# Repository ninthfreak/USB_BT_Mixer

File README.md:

# USB_BT_Mixer

A small box with two USB-C inputs and one Bluetooth audio output. Any USB-C host that supports USB audio sees each input as a normal USB sound card. The box mixes both inputs and streams the mix to any Bluetooth audio sink.

- **Architecture (start here): [`docs/architecture.md`](docs/architecture.md)**
- Decision log: [`docs/decisions.md`](docs/decisions.md)
- Design record: [`docs/HANDOFF.md`](docs/HANDOFF.md)
- Corrections since the handoff: [`docs/review-notes.md`](docs/review-notes.md)
- Design envelope (limits and extension points): [`docs/design-envelope.md`](docs/design-envelope.md)
- Viability review: [`docs/viability-review.md`](docs/viability-review.md)
- Parts list: [`hardware/BOM.csv`](hardware/BOM.csv)

Status: planning. Inputs: Waveshare RP2350-USB-C ×2, USB-C exposed directly through the enclosure (each needs an external Schottky to the shared rail). Bluetooth output: original ESP32 on a Waveshare ESP32-DEV-KIT-WROOM-32E-N4, powered from the rail via its `VSYS` pin. The ESP32 mixes and owns the audio clock. Configured from any browser via a page the box serves over USB; no case buttons. See [`docs/decisions.md`](docs/decisions.md). Firmware not started; the enclosure test coupon needs re-measuring for the new input board.

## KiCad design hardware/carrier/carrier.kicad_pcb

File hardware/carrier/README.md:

# Carrier board

> **Status: KiCad DRC clean, routed, not built, not ordered.**
>
> - **Antenna clearance: accepted as is** (owner, 2026-10-26). Copper is
>   6.55 mm in front of the antenna against Espressif's 15 mm; the antenna
>   itself hangs fully past the board edge
>   ([`AUDIT.md` #21](AUDIT.md#21-antenna-clearance-on-the-front-side-new)).
> - Recommendation before ordering: **the two-I2S clock loop-back is still
>   untested.** A jumper-wire bench test of one input board + the ESP32 would
>   prove it for the price of an afternoon.

One flat PCB that the three modules solder onto, replacing the hand-wired
loom. All passives are through-hole and live on it.

## At a glance

| | |
|---|---|
| Size | 70.0 × 79.6 mm, L-shaped (see below), 2 layers, 1.6 mm |
| Parts | U1, U2 input boards; U3 ESP32 devkit; 2 Schottky diodes; 9 resistors (R1, R3 standing); 4 capacitors; 3-pin debug header; 2 test pads |
| Nets | 22: 18 signal, 3 power (VBUS1, VBUS2, RAIL), GND |
| Rules | 0.40 mm track, 0.25 mm clearance, 0.8/0.4 mm vias, 0.5 mm copper to edge, 0.5 mm drill to drill. Loose for any fab |
| Top layer | **Every signal.** No signal changes layer: 0 signal vias |
| Bottom layer | Ground plane (89 % of the board) plus power only |
| Routing | Freerouting: 108 signal segments; rail and ground stubs by hand; 754 mm of track; 4 vias, all ground |
| Joints to solder | 40 of 70 module lands, plus the passives |

## How the board is laid out

The rules, so it reads the way it works (owner, 2026-10-27):

- **Top layer: signals.** Every signal stays on top from end to end.
- **Bottom layer: ground and power.** A solid ground plane. The rail is the
  only long track on it, running round the front and left edges behind the
  input boards' port ends, where no signal crosses it.
- **Related lines run together.** Each board's three I2S lines and its UART
  pair travel as groups.

Each input board is **turned so its native USB port faces the hosts** (the
"programming" port, whose shell hangs 1 mm past the front edge). Its PIO-USB
port faces inward, unused. See review-notes #25.

Seen from the ESP32, west to east, the board carries input 1's UART pair,
input 1's I2S group, input 2's UART pair, input 2's I2S group. The ESP32 pins
are chosen in that order (`netlist.py`). The shared clocks reach input 2 by
passing **between the pads of R2 and R4**, which lie across input 2's UART
pair, so no signal needs the bottom layer.

| Where | What |
|---|---|
| Left margin | The rail (bottom), test points |
| Strip behind input 1 | Rail bulk and bypass at the ESP32's 5V pad; input 1's clock resistors R1, R3, standing on their lanes |
| Channel between the boards | Input 1's diode, bypass and GP29 pull-down at its power pads; debug header J1; input 2's RX resistor R6 on its lane |
| Strip behind input 2 | Input 2's clock resistors R2, R4, lying across its UART pair; its GP29 and audio pull-downs |
| Right margin | Input 2's diode and bypass at its power pads |
| Behind the ESP32 | Input 1's RX resistor R5, at the ESP32's TX pin |

## Why it is an L, not a rectangle

The front must be 70 mm wide for the two input boards side by side. The ESP32
devkit sits across the back, its USB-C end hanging 1 mm past the left edge so
a flashing cable fits. That puts the antenna at the right.

Espressif's first choice is an antenna **outside** the base board, with any
board under it cut away. So the back-right corner is cut off and the
devkit's antenna end hangs 7.5 mm into free air. An L costs nothing extra:
fabs price by the bounding box.

The catch is the antenna's front side, where the front-right block comes
close: 6.55 mm, where Espressif asks for 15. The owner accepted that rather
than make the board ~8.5 mm deeper ([AUDIT.md #21](AUDIT.md#21-antenna-clearance-on-the-front-side-new)).

## Build

```sh
./build.sh                          # regenerate and check everything
/usr/bin/python3 route.py --reroute # only after moving parts or changing nets
```

Everything runs under the **system** python (`/usr/bin/python3`), which has
KiCad 7's `pcbnew` bindings. Every step must pass. The output is
byte-identical across rebuilds, so a diff means something really changed.

The build does **not** run Freerouting: its output varies from run to run.
It lays the committed result, `carrier.ses`. If the placement or netlist has
changed since that route was made, `route.py` stops and says to reroute.
Rerouting downloads Freerouting 2.1.0 once (SHA-256 checked, analytics off)
and needs Java 17 or later; it takes about 10 seconds.

`carrier.kicad_sch`, `carrier.kicad_pcb`, `carrier.pretty/`,
`CONNECTIONS.md` and the PDFs are generated. Edit `netlist.py` (connectivity)
or `gen_pcb.py` (placement) and rebuild. Never hand-edit the outputs.

## Files

| File | What |
|---|---|
| `netlist.py` | **Single source of truth** for connectivity: parts, pin maps, nets, footprints, and what is deliberately unconnected |
| `gen_fp.py` | The two module land patterns, from `enclosure/boards.scad` |
| `gen_sch.py` | `carrier.kicad_sch` |
| `gen_table.py` | `CONNECTIONS.md`: every net, and which pads to solder |
| `gen_pcb.py` | `carrier.kicad_pcb`, built with pcbnew: outline, placement, pad nets, schematic links, labels, the ground pour |
| `route.py` | Lays the rail and ground stubs by hand, every signal from `carrier.ses`; `--reroute` runs Freerouting to make a new one |
| `specctra.py` | Design export edits and session import between KiCad and Freerouting |
| `carrier.ses`, `carrier-route.json` | The committed route, and the hash of the design it was made for |
| `drc.py` | **The gate.** KiCad's own DRC with this board's rules, plus every pad's net against `netlist.py` |
| `check_footprints.py` | Recomputes every pad coordinate from `boards.scad` |
| `check_netlist.py` | Reads the netlist back out of the schematic and diffs it; checks diode and capacitor polarity against the footprint's own markings |
| `check_pcb.py` | Mechanical intent: native USB ports over the front edge, ESP32 overhangs at both ends, hole webs |
| `check_routing.py` | Routed intent: power widths, I2S chain lengths, bottom pour coverage, every signal on top |
| `AUDIT.md` | The 2026-10-26 audit and what was done about each finding |

## How it is verified

KiCad's DRC (`pcbnew.WriteDRCReport`) is the authority: clearances,
connectivity including the pour, courtyards, holes, silkscreen, keep-outs.
KiCad 7's `kicad-cli` has no DRC command, which for a while was taken to mean
no DRC was available. It was, through the Python bindings.

The custom checks cover what DRC cannot know: design intent. Each one has
been shown to **fail** on a deliberately broken board, not only to pass:

| Break | Caught by | Result |
|---|---|---|
| Diode pins mapped A=1 (the original bug) | `check_netlist.py` | 4 polarity failures |
| Delete the longest BCLK1 track | `drc.py` | 1 unconnected, 2 dangling |
| Empty the GND pour | `drc.py` | many unconnected |
| Drop a GND via onto an LRCK track | `drc.py` | clearance and hole errors |
| Track 0.3 mm from the edge | `drc.py` | edge clearance |
| Power traces at 0.4 mm | `check_routing.py` | every thin RAIL segment listed |
| A BCLK track on the bottom, a via on BCLK1 | `check_routing.py` | both listed |
| ESP32 USB-C end flush (no overhang) | `check_pcb.py` | fails |
| Antenna overhang 3 mm | `check_pcb.py` | fails |
| Input 1 turned back to 0° (PIO-USB to the hosts) | `check_pcb.py` | fails |
| R8 moved 1 mm, old route laid | `route.py` | refuses: "routed for a different placement" |

One KiCad behaviour worth knowing when testing: saving a board reassigns a
track that is not connected to its own net to whatever copper it touches (in
practice, the ground pour). A test track must therefore join two pads of its
net. DRC still catches the missing connection a reassigned track leaves.

`drc-report.txt` holds the last report. Its only entries are
"library not in this configuration" notes: the container has no global KiCad
library table. They say nothing about the copper.

## Pin numbering

We draw both the symbol and the footprint, so the numbering is ours.

**RP2350-USB-C** — component side, native ("programming") port at the top:

- pads 1–9, left edge top to bottom: `5V GND 3V3 GP29 GP28 GP27 GP26 GP10 GP9`
- pads 10–18, right edge top to bottom: `GP0 GP1 GP2 GP3 GP4 GP5 GP6 GP7 GP8`

On the carrier each input board is turned 180°, so the native port faces the
front edge, power and I2S are on the board's right-hand edge and UART/debug
on its left.

**ESP32-DEV-KIT** — pads 1–19 are header J3, pads 20–38 are J4 (so J4 pin *n*
is our pad 19 + *n*). Pads 1, 2, 20 and 21 have no land: they sit under the
antenna overhang.

## Land patterns

Both modules are castellated, so they solder flat with the iron on the
**outside** of every joint: visible, inspectable, reworkable, no reflow.

Each pad is 1.30 mm along the edge × 3.00 mm across, sticking out 1.10 mm past
the module outline. At 2.54 mm pitch that leaves 1.24 mm between pads. The
pads reference the board **outline**, so the ESP32's header row spacing never
enters the footprint.

| Footprint | +Y is |
|---|---|
| `RP2350-USB-C` | the **native USB** ("programming") port, proud of the edge. Placed at 180°, so +Y faces the front edge |
| `ESP32-DEV-KIT` | header **J3** (pads 1–19). −X is the antenna end |

Passives use stock KiCad footprints: axial resistors and DO-41 diodes at
7.62 mm, R1 and R3 standing at 2.54 mm, disc caps at 5.00 mm, the bulk cap
radial at 2.50 mm.

## Dimensions: use what is recorded

Both modules are dimensioned by Waveshare drawings, already written down in
`enclosure/boards.scad`. **Do not ask the owner to re-measure them.** Both
modules are flat underneath (owner, boards in hand).

## Soldering: not every pad

Solder only the pads that carry a net, plus a few corners so nothing can peel.
**40 joints instead of 70.** `CONNECTIONS.md` has the per-pad map.
`check_netlist.py` asserts every mechanical pad floats; several are the
ESP32's flash and strapping pins, and tying those to live copper would be
worse than leaving them bare.

The full land pattern is still made, so any pad can be soldered later.

### Plug forces

With the native port at the front, each input board's first pads are 2.88 mm
from its USB-C shell, and the soldered 5V, GND and GP0 joints sit at that
end. They take some of a cable's peel moment, but solder is still the wrong
thing to rely on: whatever enclosure holds the carrier should bear on the
modules near the port.

## Programming with everything soldered

- **Input boards:** through the front USB-C port (native USB). First flash:
  hold BOOT while plugging in and copy the UF2. BOOT is on the board's top
  face. After that, firmware can reboot into its bootloader on command.
- **ESP32:** through its own USB-C, hanging past the left edge; no buttons
  needed, and the box can stay powered.

Details: `hardware/wiring.md`, "Programming with everything soldered".

## Deliberate design choices

- **The two 3V3 rails are never tied together.** Each module has its own
  regulator. Asserted in `NO_CONNECT`.
- **Each input board reaches the rail only through its own Schottky**, so the
  two hosts' 5 V supplies never meet.
- **1 kΩ in series with every line the ESP32 drives into an input board**
  (BCLK, LRCK, UART TX). With one host connected, the other input board is
  unpowered; this keeps injection to ~3 mA per pin.
- **Never IO36/IO39** for I2S: they glitch when the ADC powers up (Espressif
  erratum; reported during A2DP streaming). The loop-backs are IO26→IO25 and
  IO14→IO33.
- **GP29 pulled down through 4.7 kΩ** (R8/R9), not a solder bridge. Leave the
  resistor out to free the pin.
- **100 kΩ pull-down on AUD2**: GPIO35 has no internal pull and would float
  with input 2 absent. AUD1 (GPIO13) uses its internal pull-down.
- **TP1/TP2** (rail and ground, 3 mm apart in the left margin) because the
  rail voltage is an estimate that must be measured on the built box
  (review-notes #18).

## Still open

| Item | State |
|---|---|
| Antenna clearance, front side | **Accepted as is** (owner). If Bluetooth range disappoints, option C in [AUDIT.md #21](AUDIT.md#21-antenna-clearance-on-the-front-side-new) is the fix |
| I2S loop-back and UART relay | **Untested** in hardware. Bench test before ordering (recommended) |
| Enclosure for the carrier | Not designed. Its port wall must take the native port's **proud** shell (the old box expected a flush one); the carrier needs standoffs because through-hole leads protrude underneath |
| Native-USB shell overhang | 1.00 mm assumed (`usb_over_in`); worth a caliper check before the enclosure |
| ESP32 sources | The dimensioned drawing is archived (`docs/sources/esp32-dev-kit-drawing.png`). The schematic PDF is still not in the repo. Not a blocker |

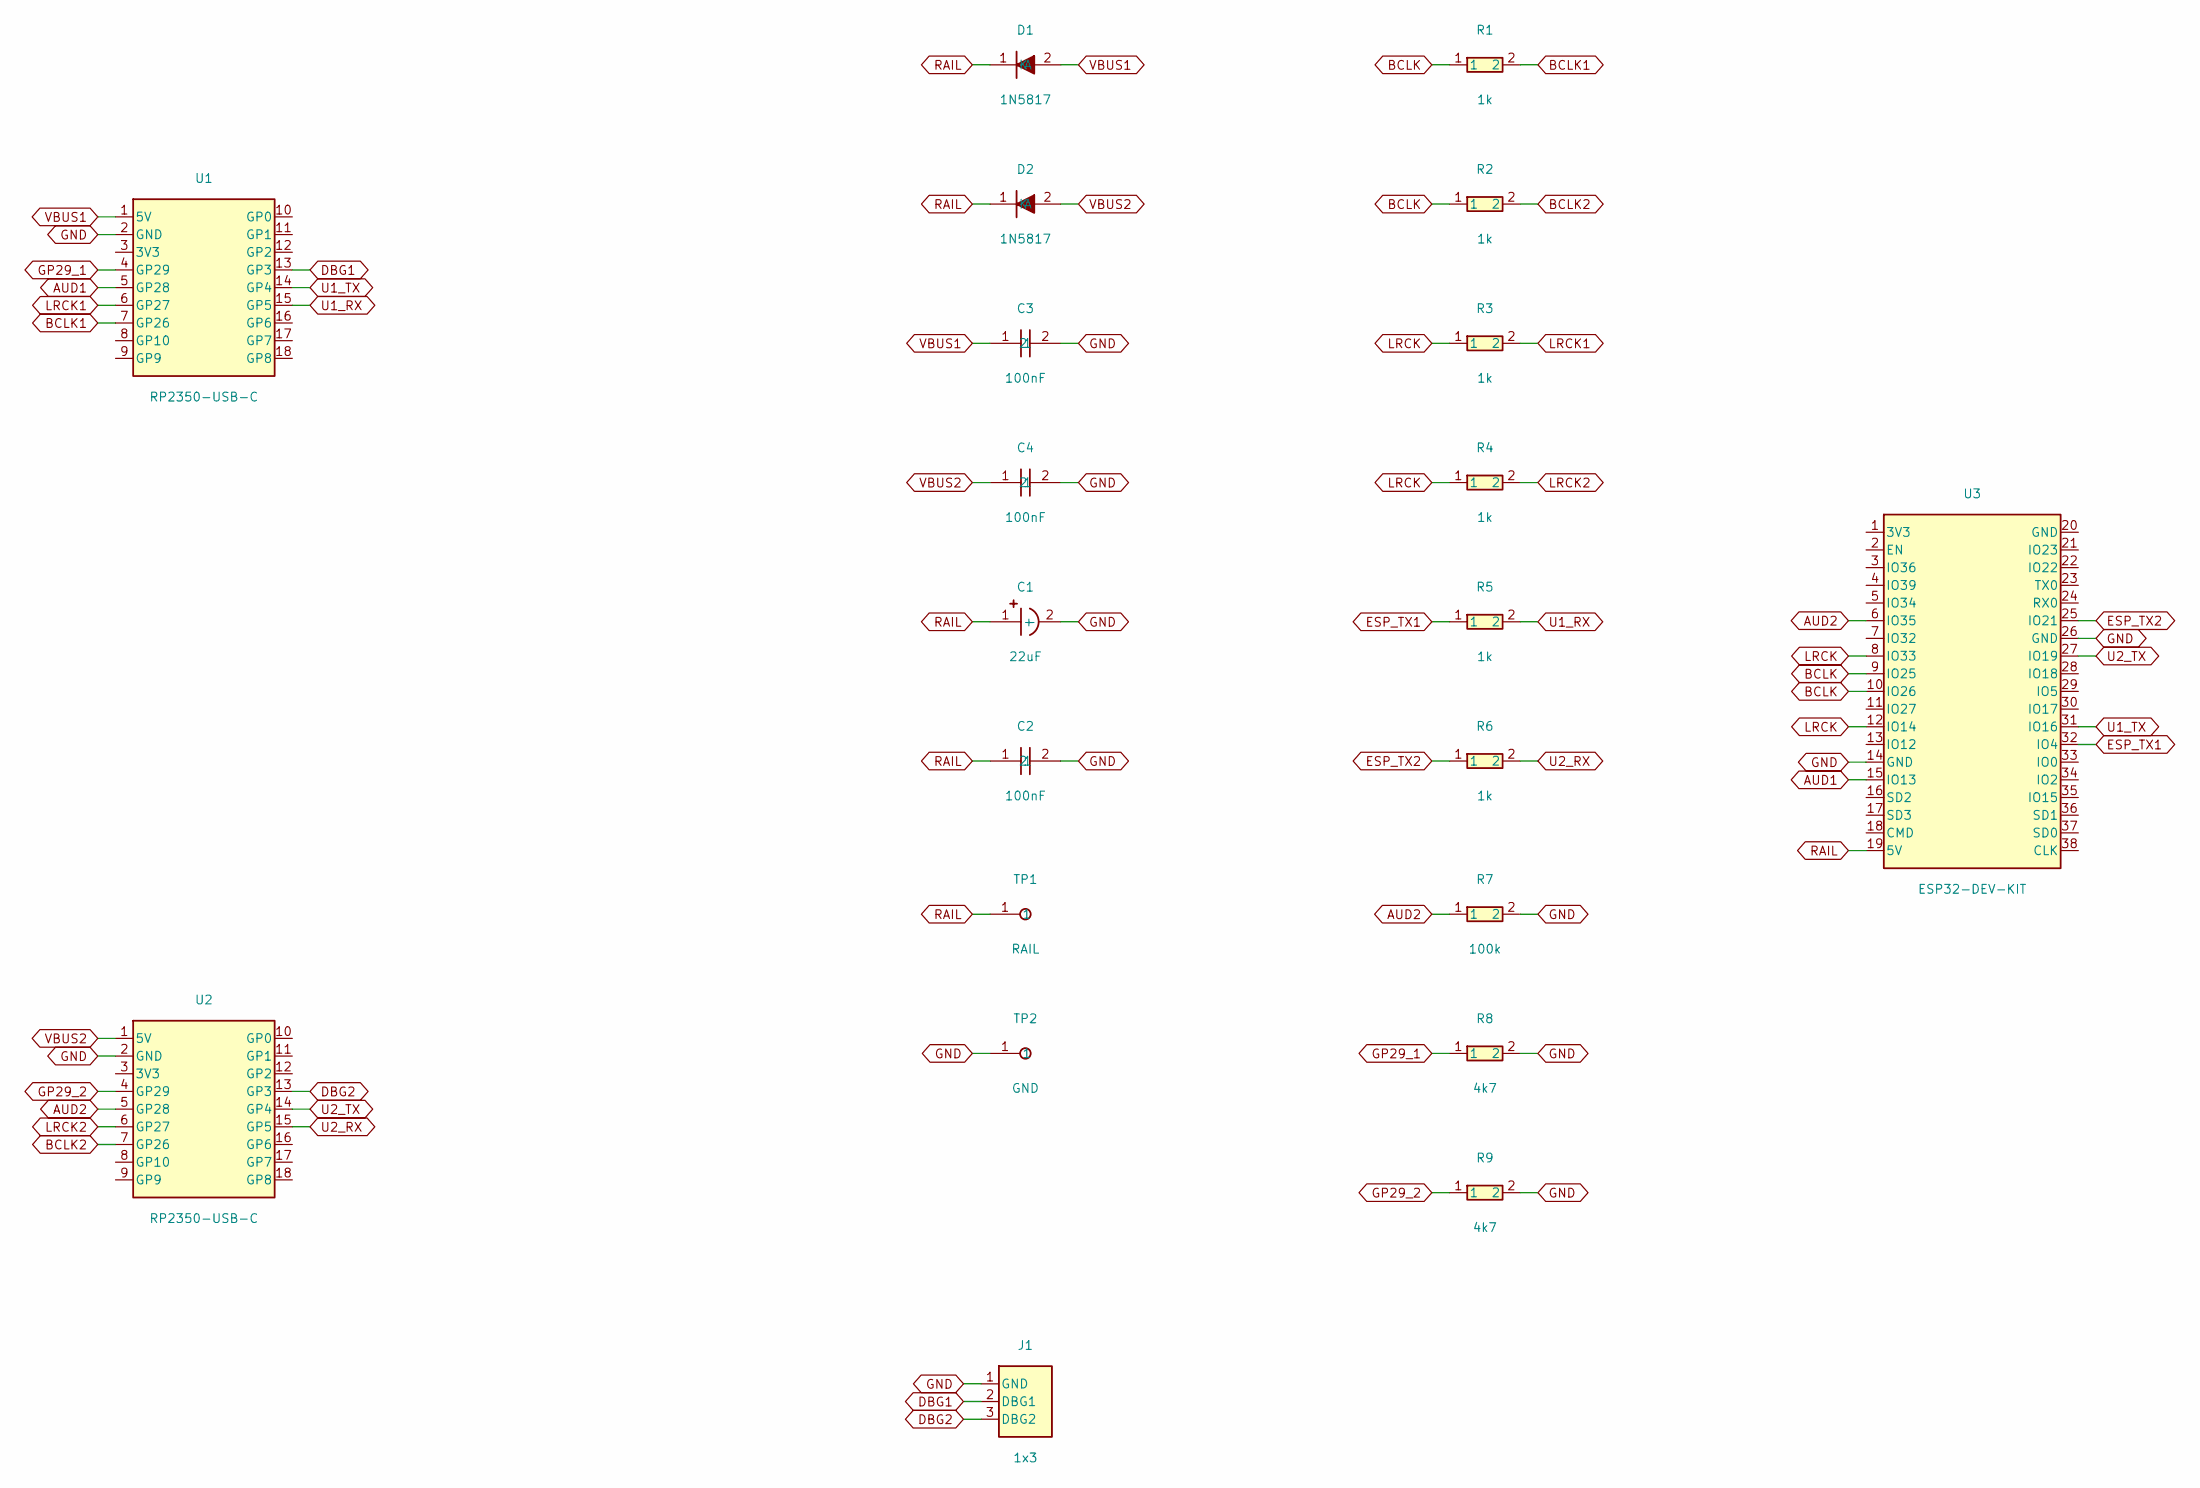
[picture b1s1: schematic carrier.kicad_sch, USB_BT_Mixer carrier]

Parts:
C1: 22uF; CP_Radial_D5.0mm_P2.50mm
C2, C3, C4: 100nF; C_Disc_D5.0mm_W2.5mm_P5.00mm
D1, D2: 1N5817; D_DO-41_SOD81_P7.62mm_Horizontal
J1: 1x3; PinHeader_1x03_P2.54mm_Vertical
R1, R3: 1k; R_Axial_DIN0207_L6.3mm_D2.5mm_P2.54mm_Vertical
R2, R4, R5, R6: 1k; R_Axial_DIN0207_L6.3mm_D2.5mm_P7.62mm_Horizontal
R7: 100k; R_Axial_DIN0207_L6.3mm_D2.5mm_P7.62mm_Horizontal
R8, R9: 4k7; R_Axial_DIN0207_L6.3mm_D2.5mm_P7.62mm_Horizontal
TP1: RAIL; TestPoint_Pad_D1.5mm
TP2: GND; TestPoint_Pad_D1.5mm
U1, U2: RP2350-USB-C
U3: ESP32-DEV-KIT

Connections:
AUD1: U1.5 (GP28), U3.15 (IO13)
AUD2: R7.1, U2.5 (GP28), U3.6 (IO35)
BCLK: R1.1, R2.1, U3.9 (IO25), U3.10 (IO26)
BCLK1: R1.2, U1.7 (GP26)
BCLK2: R2.2, U2.7 (GP26)
DBG1: J1.2 (DBG1), U1.13 (GP3)
DBG2: J1.3 (DBG2), U2.13 (GP3)
ESP_TX1: R5.1, U3.32 (IO4)
ESP_TX2: R6.1, U3.25 (IO21)
GND: C1.2 (-), C2.2, C3.2, C4.2, J1.1 (GND), R7.2, R8.2, R9.2, TP2.1, U1.2 (GND), U2.2 (GND), U3.14 (GND), U3.26 (GND)
GP29_1: R8.1, U1.4 (GP29)
GP29_2: R9.1, U2.4 (GP29)
LRCK: R3.1, R4.1, U3.8 (IO33), U3.12 (IO14)
LRCK1: R3.2, U1.6 (GP27)
LRCK2: R4.2, U2.6 (GP27)
RAIL: C1.1 (+), C2.1, D1.1 (K), D2.1 (K), TP1.1, U3.19 (5V)
U1_RX: R5.2, U1.15 (GP5)
U1_TX: U1.14 (GP4), U3.31 (IO16)
U2_RX: R6.2, U2.15 (GP5)
U2_TX: U2.14 (GP4), U3.27 (IO19)
VBUS1: C3.1, D1.2 (A), U1.1 (5V)
VBUS2: C4.1, D2.2 (A), U2.1 (5V)

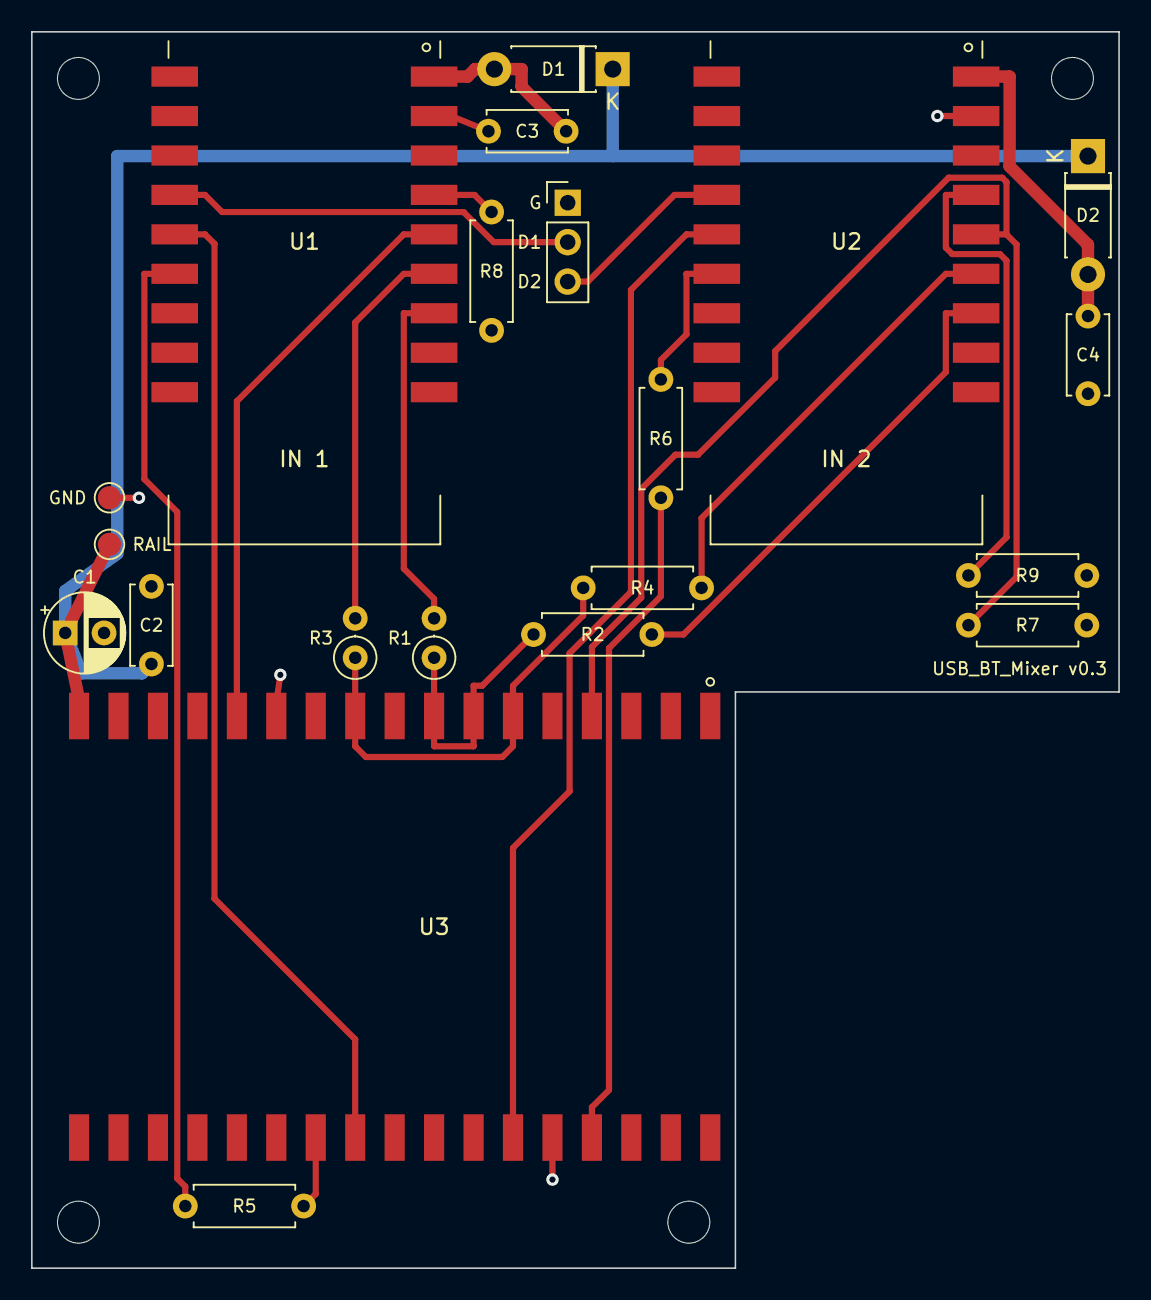
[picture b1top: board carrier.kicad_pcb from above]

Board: 2 copper layers, 70.0 x 79.6 mm, 25 parts (0 on the bottom side), 22 nets.

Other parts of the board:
H1, H2, H3, H4: MountingHole_2.7mm_M2.5

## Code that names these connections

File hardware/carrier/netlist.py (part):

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    "R4": dict(kind="r", value="1k", desc="LRCK series to input 2; limits back-feed"),
    "R5": dict(kind="r", value="1k", desc="UART TX series to input 1; limits back-feed"),
    "R6": dict(kind="r", value="1k", desc="UART TX series to input 2; limits back-feed"),
    "R7": dict(kind="r", value="100k", desc="AUD2 pull-down: GPIO35 has no internal pull"),
    # 4.7k rather than a solder bridge: a bridge is a dead short if firmware
    # ever drives GP29 high. 4.7k holds it firmly low against the RP2350-E9
    # input leakage (up to ~120 uA, 0.56 V). Leave unfitted to free the pin.
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    "C4": dict(kind="c", value="100nF", desc="Input 2 supply bypass"),

    "J1": dict(kind="hdr", value="1x3", desc="Debug serial breakout",
               pins=["GND", "DBG1", "DBG2"]),
    "TP1": dict(kind="tp", value="RAIL", desc="Rail test point -- MEASURE here"),
    "TP2": dict(kind="tp", value="GND", desc="Ground test point"),
}
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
